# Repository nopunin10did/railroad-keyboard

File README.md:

# The Railroad Keyboard
PCB and Plate Repository

A long keyboard with ortholinear alphas and semi-standard modifier keys. For more information, join the [NoPunIn10Key Discord](https://discord.gg/7AcdaNw5Fn).

* Keyboard Maintainer: [NoPunIn10Did](https://nopunin10did.com)
* Hardware Supported: The Railroad: 2020-07 Prototype

This repository contains the KiCad files for the PCB, switch plate, and bottom plate. It also contains the BOM files that I used when ordering it from JLCPCB.

This work (Railroad Keyboard) is licensed under a [Creative Commons Attribution-ShareAlike 4.0 International License](https://creativecommons.org/licenses/by-sa/4.0/).

All other rights are reserved by NoPunIn10Did LLC.

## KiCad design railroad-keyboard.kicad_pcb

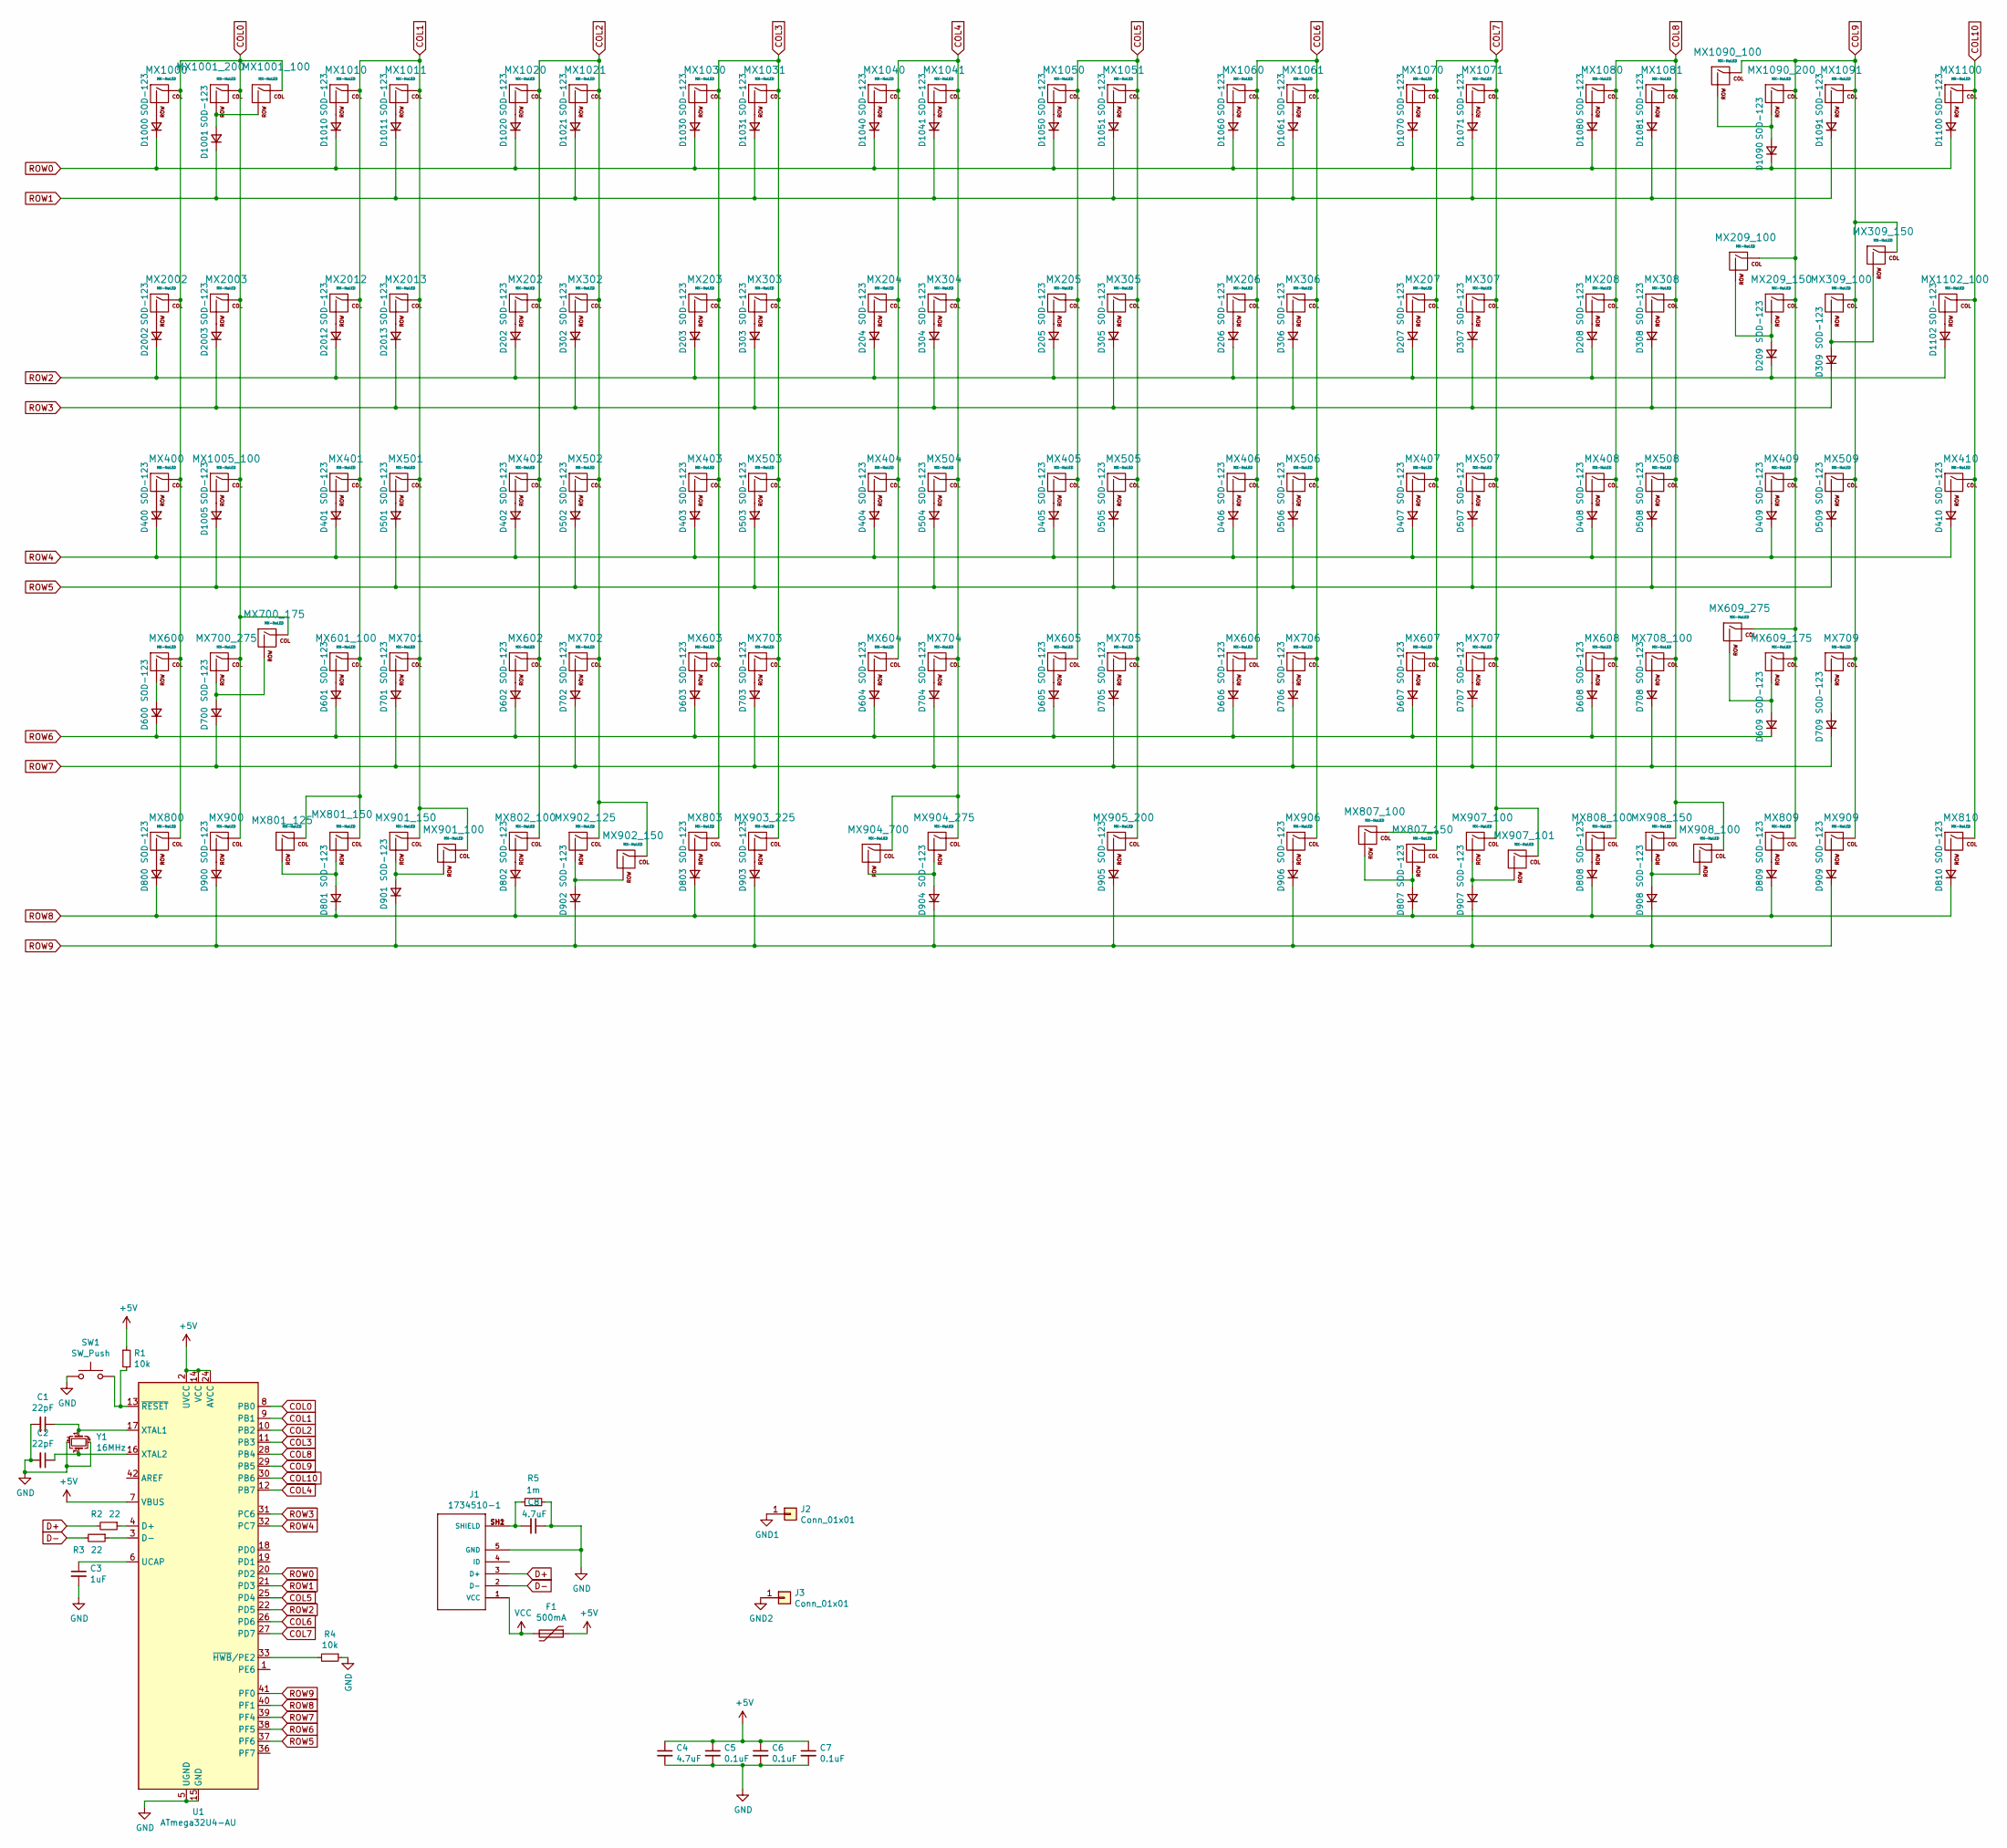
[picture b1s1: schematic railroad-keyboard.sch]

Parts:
C1, C2: 22pF; C_0805_2012Metric
C3: 1uF; C_0805_2012Metric
C4, C8: 4.7uF; C_0805_2012Metric
C5, C6, C7: 0.1uF; C_0805_2012Metric
D202, D203, D204, D205, D206, D207, D208, D209, D302, D303, D304, D305, D306, D307, D308, D309, D400, D401, D402, D403, D404, D405, D406, D407, D408, D409, D410, D501, D502, D503, D504, D505, D506, D507, D508, D509, D600, D601, D602, D603, D604, D605, D606, D607, D608, D609, D700, D701, D702, D703, D704, D705, D706, D707, D708, D709, D800, D801, D802, D803, D807, D808, D809, D810, D900, D901, D902, D903, D904, D905, D906, D907, D908, D909, D1000, D1001, D1005, D1010, D1011, D1020, D1021, D1030, D1031, D1040, D1041, D1050, D1051, D1060, D1061, D1070, D1071, D1080, D1081, D1090, D1091, D1100, D1102, D2002, D2003, D2012, D2013: SOD-123; D_SOD-123
F1: 500mA; Fuse_1206_3216Metric
J1: 1734510-1; TE_1734510-1
J2, J3: Conn_01x01; PinHeader_1x01_P1.00mm_Horizontal
MX202, MX203, MX204, MX205, MX206, MX207, MX208, MX209_100, MX302, MX303, MX304, MX305, MX306, MX307, MX308, MX309_100, MX402, MX403, MX404, MX405, MX406, MX407, MX408, MX409, MX501, MX502, MX503, MX504, MX505, MX506, MX507, MX508, MX600, MX601_100, MX602, MX603, MX604, MX605, MX606, MX607, MX608, MX701, MX702, MX703, MX704, MX705, MX706, MX707, MX708_100, MX709, MX800, MX802_100, MX803, MX807_100, MX808_100, MX809, MX810, MX900, MX901_100, MX906, MX907_100, MX907_101, MX908_100, MX909, MX1000, MX1001_100, MX1005_100, MX1010, MX1011, MX1020, MX1021, MX1030, MX1031, MX1040, MX1041, MX1050, MX1051, MX1060, MX1061, MX1070, MX1071, MX1080, MX1081, MX1090_100, MX1091, MX1100, MX1102_100, MX2002, MX2013: MX-NoLED; MXOnly-1U-NoLED
MX209_150, MX309_150, MX801_150, MX807_150, MX901_150, MX902_150, MX908_150, MX2003, MX2012: MX-NoLED; MXOnly-1.5U-NoLED
MX400, MX801_125, MX902_125: MX-NoLED; MXOnly-1.25U-NoLED
MX401, MX903_225: MX-NoLED; MXOnly-2.25U-NoLED
MX410: MX-NoLED; MXOnly-ISO-ROTATED-ReversedStabilizers-NoLED
MX509, MX609_175, MX700_175: MX-NoLED; MXOnly-1.75U-NoLED
MX609_275, MX700_275: MX-NoLED; MXOnly-2.75U-NoLED
MX904_275: MX-NoLED; MXOnly-2.75U-ReversedStabilizers-NoLED
MX904_700: MX-NoLED; MXOnly-7U-NoLED
MX905_200, MX1001_200, MX1090_200: MX-NoLED; MXOnly-2U-NoLED
R1, R4: 10k; R_0805_2012Metric
R2, R3: 22; R_0805_2012Metric
R5: 1m; R_0805_2012Metric
SW1: SW_Push; SW_Tactile_SPST_Angled_MJTP1117
U1: ATmega32U4-AU; TQFP-44_10x10mm_P0.8mm
Y1: 16MHz; Crystal_SMD_3225-4Pin_3.2x2.5mm

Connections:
+5V: C4.1, C5.1, C6.1, C7.1, F1.1, R1.1, U1.2 (UVCC), U1.7 (VBUS), U1.14 (VCC), U1.24 (AVCC), U1.34 (VCC), U1.44 (AVCC)
COL0: MX400.1 (COL), MX600.1 (COL), MX700_175.1 (COL), MX700_275.1 (COL), MX800.1 (COL), MX900.1 (COL), MX1000.1 (COL), MX1001_100.1 (COL), MX1001_200.1 (COL), MX1005_100.1 (COL), MX2002.1 (COL), MX2003.1 (COL), U1.8 (PB0); also elsewhere on the board
COL1: MX401.1 (COL), MX501.1 (COL), MX601_100.1 (COL), MX701.1 (COL), MX801_125.1 (COL), MX801_150.1 (COL), MX901_100.1 (COL), MX901_150.1 (COL), MX1010.1 (COL), MX1011.1 (COL), MX2012.1 (COL), MX2013.1 (COL), U1.9 (PB1); also elsewhere on the board
COL2: MX202.1 (COL), MX302.1 (COL), MX402.1 (COL), MX502.1 (COL), MX602.1 (COL), MX702.1 (COL), MX802_100.1 (COL), MX902_125.1 (COL), MX902_150.1 (COL), MX1020.1 (COL), MX1021.1 (COL), U1.10 (PB2)
COL3: MX203.1 (COL), MX303.1 (COL), MX403.1 (COL), MX503.1 (COL), MX603.1 (COL), MX703.1 (COL), MX803.1 (COL), MX903_225.1 (COL), MX1030.1 (COL), MX1031.1 (COL), U1.11 (PB3)
COL4: MX204.1 (COL), MX304.1 (COL), MX404.1 (COL), MX504.1 (COL), MX604.1 (COL), MX704.1 (COL), MX904_275.1 (COL), MX904_700.1 (COL), MX1040.1 (COL), MX1041.1 (COL), U1.12 (PB7)
COL5: MX205.1 (COL), MX305.1 (COL), MX405.1 (COL), MX505.1 (COL), MX605.1 (COL), MX705.1 (COL), MX905_200.1 (COL), MX1050.1 (COL), MX1051.1 (COL), U1.25 (PD4)
COL6: MX206.1 (COL), MX306.1 (COL), MX406.1 (COL), MX506.1 (COL), MX606.1 (COL), MX706.1 (COL), MX906.1 (COL), MX1060.1 (COL), MX1061.1 (COL), U1.26 (PD6)
COL7: MX207.1 (COL), MX307.1 (COL), MX407.1 (COL), MX507.1 (COL), MX607.1 (COL), MX707.1 (COL), MX807_100.1 (COL), MX807_150.1 (COL), MX907_100.1 (COL), MX907_101.1 (COL), MX1070.1 (COL), MX1071.1 (COL), U1.27 (PD7)
COL8: MX208.1 (COL), MX308.1 (COL), MX408.1 (COL), MX508.1 (COL), MX608.1 (COL), MX708_100.1 (COL), MX808_100.1 (COL), MX908_100.1 (COL), MX908_150.1 (COL), MX1080.1 (COL), MX1081.1 (COL), U1.28 (PB4)
COL9: MX209_100.1 (COL), MX209_150.1 (COL), MX309_100.1 (COL), MX309_150.1 (COL), MX409.1 (COL), MX509.1 (COL), MX609_175.1 (COL), MX609_275.1 (COL), MX709.1 (COL), MX809.1 (COL), MX909.1 (COL), MX1090_100.1 (COL), MX1090_200.1 (COL), MX1091.1 (COL), U1.29 (PB5)
COL10: MX410.1 (COL), MX810.1 (COL), MX1100.1 (COL), MX1102_100.1 (COL), U1.30 (PB6)
D+: J1.3 (D+), R2.2
D-: J1.2 (D-), R3.2
GND: C1.2, C2.2, C3.2, C4.2, C5.2, C6.2, C7.2, C8.1, J1.5 (GND), R4.1, R5.2, SW1.1, U1.5 (UGND), U1.15 (GND), U1.23 (GND), U1.35 (GND), U1.43 (GND), Y1.2, Y1.4
GND1: J2.1
GND2: J3.1
unnamed: C1.1, U1.17 (XTAL1), Y1.1
unnamed: C2.1, U1.16 (XTAL2), Y1.3
unnamed: C3.1, U1.6 (UCAP)
unnamed: C8.2, J1.SH1 (SHIELD), J1.SH2 (SHIELD), R5.1
unnamed: D202.2 (A), MX202.2 (ROW)
unnamed: D203.2 (A), MX203.2 (ROW)
unnamed: D204.2 (A), MX204.2 (ROW)
unnamed: D205.2 (A), MX205.2 (ROW)
unnamed: D206.2 (A), MX206.2 (ROW)
unnamed: D207.2 (A), MX207.2 (ROW)
unnamed: D208.2 (A), MX208.2 (ROW)
unnamed: D209.2 (A), MX209_100.2 (ROW), MX209_150.2 (ROW)
unnamed: D302.2 (A), MX302.2 (ROW)
unnamed: D303.2 (A), MX303.2 (ROW)
unnamed: D304.2 (A), MX304.2 (ROW)
unnamed: D305.2 (A), MX305.2 (ROW)
unnamed: D306.2 (A), MX306.2 (ROW)
unnamed: D307.2 (A), MX307.2 (ROW)
unnamed: D308.2 (A), MX308.2 (ROW)
unnamed: D309.2 (A), MX309_100.2 (ROW), MX309_150.2 (ROW)
unnamed: D400.2 (A), MX400.2 (ROW)
unnamed: D401.2 (A), MX401.2 (ROW)
unnamed: D402.2 (A), MX402.2 (ROW)
unnamed: D403.2 (A), MX403.2 (ROW)
unnamed: D404.2 (A), MX404.2 (ROW)
unnamed: D405.2 (A), MX405.2 (ROW)
unnamed: D406.2 (A), MX406.2 (ROW)
unnamed: D407.2 (A), MX407.2 (ROW)
unnamed: D408.2 (A), MX408.2 (ROW)
unnamed: D409.2 (A), MX409.2 (ROW)
unnamed: D410.2 (A), MX410.2 (ROW)
unnamed: D501.2 (A), MX501.2 (ROW)
unnamed: D502.2 (A), MX502.2 (ROW)
unnamed: D503.2 (A), MX503.2 (ROW)
unnamed: D504.2 (A), MX504.2 (ROW)
unnamed: D505.2 (A), MX505.2 (ROW)
unnamed: D506.2 (A), MX506.2 (ROW)
unnamed: D507.2 (A), MX507.2 (ROW)
unnamed: D508.2 (A), MX508.2 (ROW)
unnamed: D509.2 (A), MX509.2 (ROW)
unnamed: D600.2 (A), MX600.2 (ROW)
unnamed: D601.2 (A), MX601_100.2 (ROW)
unnamed: D602.2 (A), MX602.2 (ROW)
unnamed: D603.2 (A), MX603.2 (ROW)
unnamed: D604.2 (A), MX604.2 (ROW)
unnamed: D605.2 (A), MX605.2 (ROW)
unnamed: D606.2 (A), MX606.2 (ROW)
unnamed: D607.2 (A), MX607.2 (ROW)
unnamed: D608.2 (A), MX608.2 (ROW)
unnamed: D609.2 (A), MX609_175.2 (ROW), MX609_275.2 (ROW)
unnamed: D700.2 (A), MX700_175.2 (ROW), MX700_275.2 (ROW)
unnamed: D701.2 (A), MX701.2 (ROW)
unnamed: D702.2 (A), MX702.2 (ROW)
unnamed: D703.2 (A), MX703.2 (ROW)
unnamed: D704.2 (A), MX704.2 (ROW)
unnamed: D705.2 (A), MX705.2 (ROW)
unnamed: D706.2 (A), MX706.2 (ROW)
unnamed: D707.2 (A), MX707.2 (ROW)
unnamed: D708.2 (A), MX708_100.2 (ROW)
unnamed: D709.2 (A), MX709.2 (ROW)
unnamed: D800.2 (A), MX800.2 (ROW)
unnamed: D801.2 (A), MX801_125.2 (ROW), MX801_150.2 (ROW)
unnamed: D802.2 (A), MX802_100.2 (ROW)
unnamed: D803.2 (A), MX803.2 (ROW)
unnamed: D807.2 (A), MX807_100.2 (ROW), MX807_150.2 (ROW)
unnamed: D808.2 (A), MX808_100.2 (ROW)
unnamed: D809.2 (A), MX809.2 (ROW)
unnamed: D810.2 (A), MX810.2 (ROW)
unnamed: D900.2 (A), MX900.2 (ROW)
unnamed: D901.2 (A), MX901_100.2 (ROW), MX901_150.2 (ROW)
unnamed: D902.2 (A), MX902_125.2 (ROW), MX902_150.2 (ROW)
unnamed: D903.2 (A), MX903_225.2 (ROW)
unnamed: D904.2 (A), MX904_275.2 (ROW), MX904_700.2 (ROW)
unnamed: D905.2 (A), MX905_200.2 (ROW)
unnamed: D906.2 (A), MX906.2 (ROW)
unnamed: D907.2 (A), MX907_100.2 (ROW), MX907_101.2 (ROW)
unnamed: D908.2 (A), MX908_100.2 (ROW), MX908_150.2 (ROW)
unnamed: D909.2 (A), MX909.2 (ROW)
unnamed: D1000.2 (A), MX1000.2 (ROW)
unnamed: D1001.2 (A), MX1001_100.2 (ROW), MX1001_200.2 (ROW)
unnamed: D1005.2 (A), MX1005_100.2 (ROW)
unnamed: D1010.2 (A), MX1010.2 (ROW)
unnamed: D1011.2 (A), MX1011.2 (ROW)
unnamed: D1020.2 (A), MX1020.2 (ROW)
unnamed: D1021.2 (A), MX1021.2 (ROW)
unnamed: D1030.2 (A), MX1030.2 (ROW)
unnamed: D1031.2 (A), MX1031.2 (ROW)
unnamed: D1040.2 (A), MX1040.2 (ROW)
unnamed: D1041.2 (A), MX1041.2 (ROW)
unnamed: D1050.2 (A), MX1050.2 (ROW)
unnamed: D1051.2 (A), MX1051.2 (ROW)
unnamed: D1060.2 (A), MX1060.2 (ROW)
unnamed: D1061.2 (A), MX1061.2 (ROW)
unnamed: D1070.2 (A), MX1070.2 (ROW)
unnamed: D1071.2 (A), MX1071.2 (ROW)
unnamed: D1080.2 (A), MX1080.2 (ROW)
unnamed: D1081.2 (A), MX1081.2 (ROW)
unnamed: D1090.2 (A), MX1090_100.2 (ROW), MX1090_200.2 (ROW)
unnamed: D1091.2 (A), MX1091.2 (ROW)
unnamed: D1100.2 (A), MX1100.2 (ROW)
unnamed: D1102.2 (A), MX1102_100.2 (ROW)
unnamed: D2002.2 (A), MX2002.2 (ROW)
unnamed: D2003.2 (A), MX2003.2 (ROW)
unnamed: D2012.2 (A), MX2012.2 (ROW)
unnamed: D2013.2 (A), MX2013.2 (ROW)
unnamed: R1.2, SW1.2, U1.13 (~RESET)
unnamed: R2.1, U1.4 (D+)
unnamed: R3.1, U1.3 (D-)
unnamed: R4.2, U1.33 (~HWB~/PE2)
ROW0: D1000.1 (K), D1010.1 (K), D1020.1 (K), D1030.1 (K), D1040.1 (K), D1050.1 (K), D1060.1 (K), D1070.1 (K), D1080.1 (K), D1090.1 (K), D1100.1 (K), U1.20 (PD2)
ROW1: D1001.1 (K), D1011.1 (K), D1021.1 (K), D1031.1 (K), D1041.1 (K), D1051.1 (K), D1061.1 (K), D1071.1 (K), D1081.1 (K), D1091.1 (K), U1.21 (PD3)
ROW2: D202.1 (K), D203.1 (K), D204.1 (K), D205.1 (K), D206.1 (K), D207.1 (K), D208.1 (K), D209.1 (K), D1102.1 (K), D2002.1 (K), D2012.1 (K), U1.22 (PD5); also elsewhere on the board
ROW3: D302.1 (K), D303.1 (K), D304.1 (K), D305.1 (K), D306.1 (K), D307.1 (K), D308.1 (K), D309.1 (K), D2003.1 (K), D2013.1 (K), U1.31 (PC6); also elsewhere on the board
ROW4: D400.1 (K), D401.1 (K), D402.1 (K), D403.1 (K), D404.1 (K), D405.1 (K), D406.1 (K), D407.1 (K), D408.1 (K), D409.1 (K), D410.1 (K), U1.32 (PC7)
ROW5: D501.1 (K), D502.1 (K), D503.1 (K), D504.1 (K), D505.1 (K), D506.1 (K), D507.1 (K), D508.1 (K), D509.1 (K), D1005.1 (K), U1.37 (PF6); also elsewhere on the board
ROW6: D600.1 (K), D601.1 (K), D602.1 (K), D603.1 (K), D604.1 (K), D605.1 (K), D606.1 (K), D607.1 (K), D608.1 (K), D609.1 (K), U1.38 (PF5)
ROW7: D700.1 (K), D701.1 (K), D702.1 (K), D703.1 (K), D704.1 (K), D705.1 (K), D706.1 (K), D707.1 (K), D708.1 (K), D709.1 (K), U1.39 (PF4)
ROW8: D800.1 (K), D801.1 (K), D802.1 (K), D803.1 (K), D807.1 (K), D808.1 (K), D809.1 (K), D810.1 (K), U1.40 (PF1)
ROW9: D900.1 (K), D901.1 (K), D902.1 (K), D903.1 (K), D904.1 (K), D905.1 (K), D906.1 (K), D907.1 (K), D908.1 (K), D909.1 (K), U1.41 (PF0)
VCC: F1.2, J1.1 (VCC)

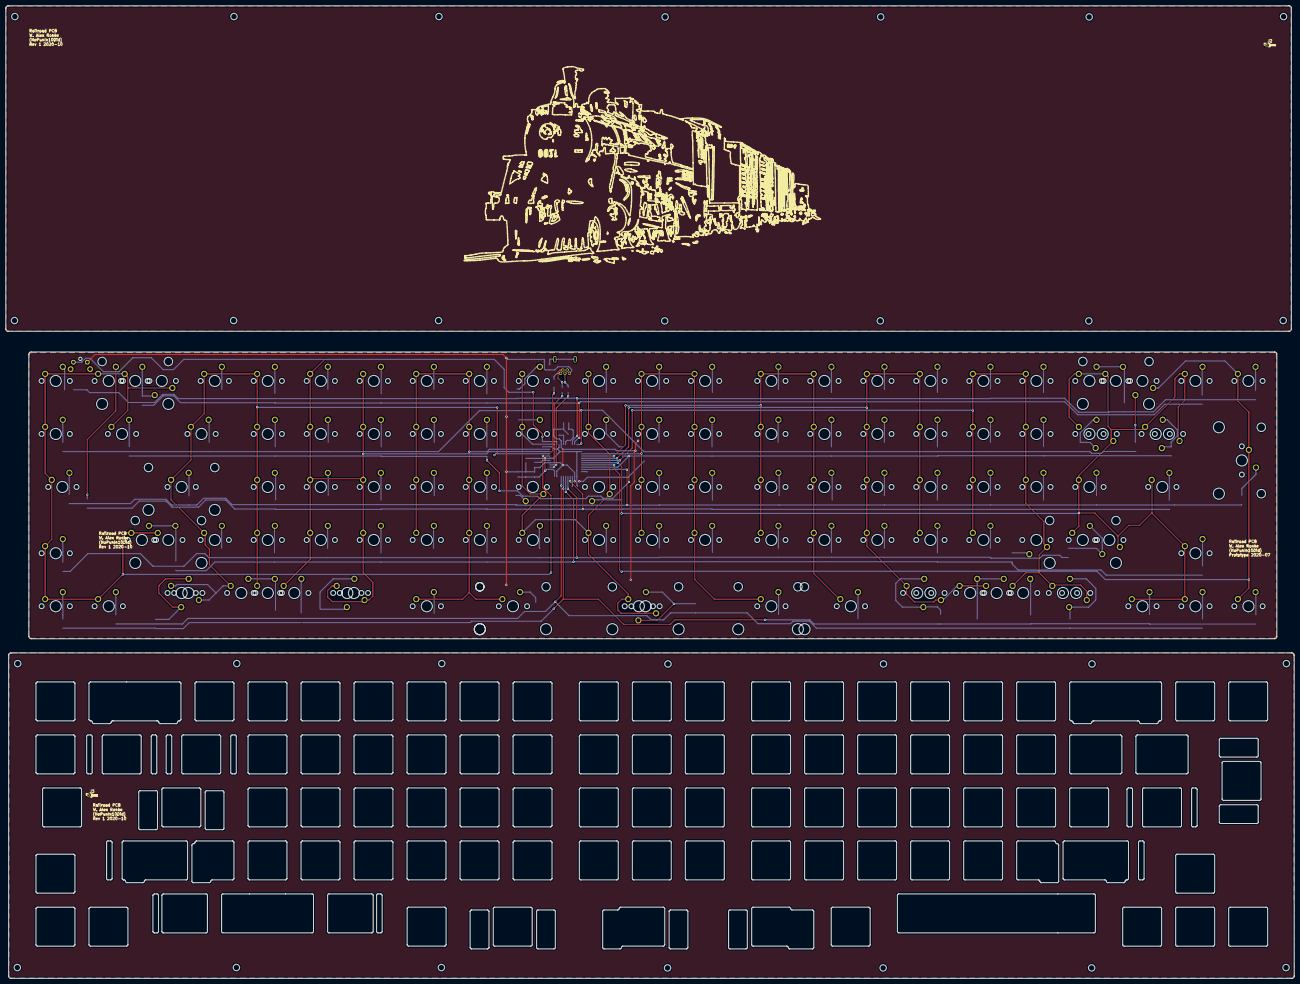
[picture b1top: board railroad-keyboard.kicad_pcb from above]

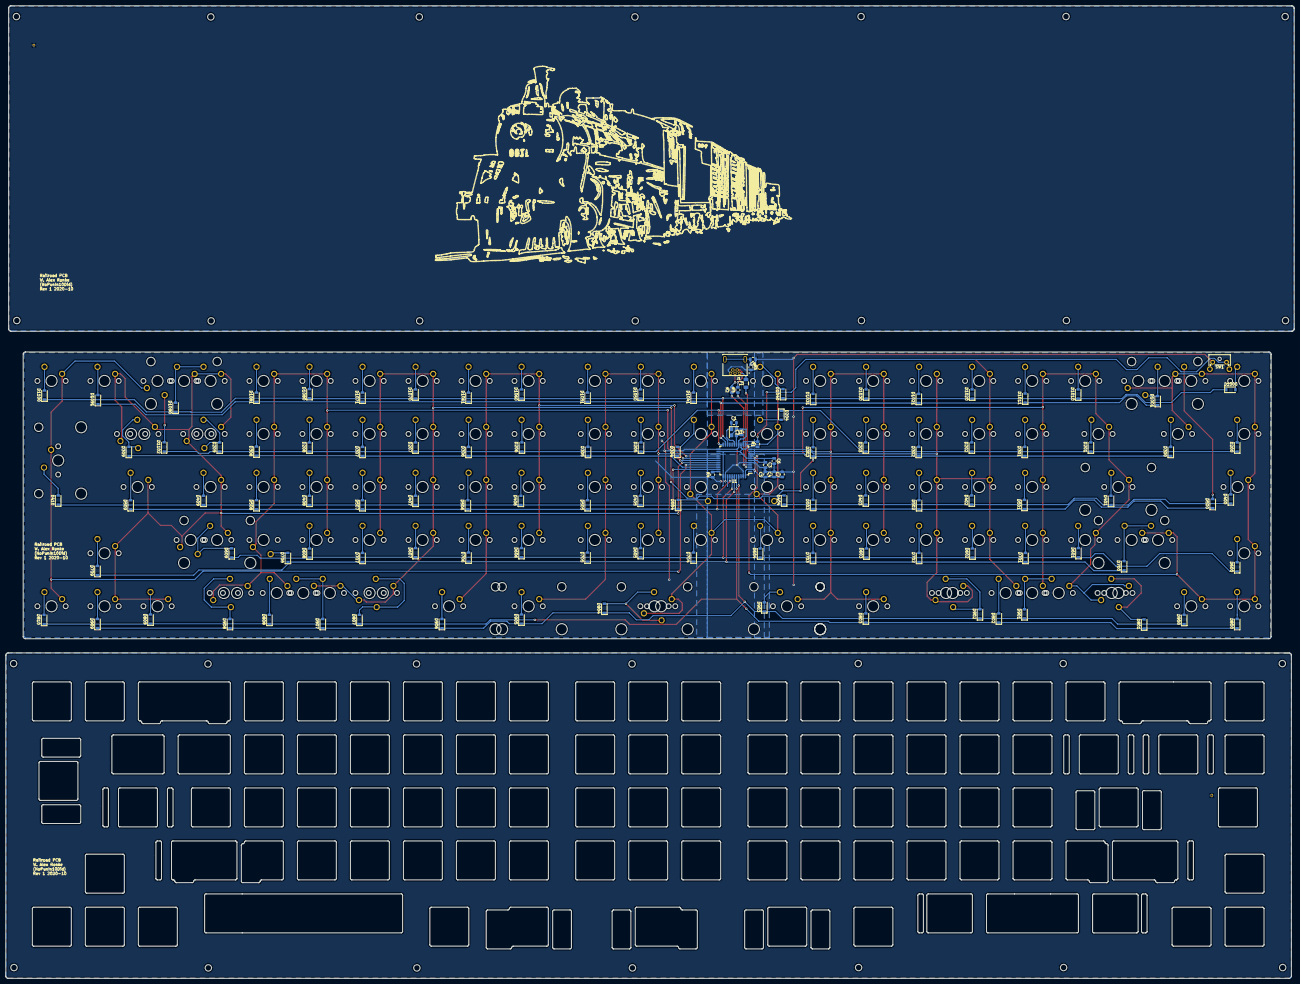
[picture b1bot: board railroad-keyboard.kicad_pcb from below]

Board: 2 copper layers, 448.5 x 103.0 mm, 235 parts (119 on the bottom side), 135 nets.

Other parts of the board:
D200, D201, D300, D301, D500: SOD-123; D_SOD-123
MX200, MX301, MX500_100: MX-NoLED; MXOnly-1U-NoLED
MX201, MX300: MX-NoLED; MXOnly-1.5U-NoLED

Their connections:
COL0: MX200.1, MX300.1, MX500_100.1; also elsewhere on the board
COL1: MX201.1, MX301.1; also elsewhere on the board
unnamed: D200.2, MX200.2
unnamed: D201.2, MX201.2
unnamed: D300.2, MX300.2
unnamed: D301.2, MX301.2
unnamed: D500.2, MX500_100.2
ROW2: D200.1, D201.1; also elsewhere on the board
ROW3: D300.1, D301.1; also elsewhere on the board
ROW5: D500.1; also elsewhere on the board

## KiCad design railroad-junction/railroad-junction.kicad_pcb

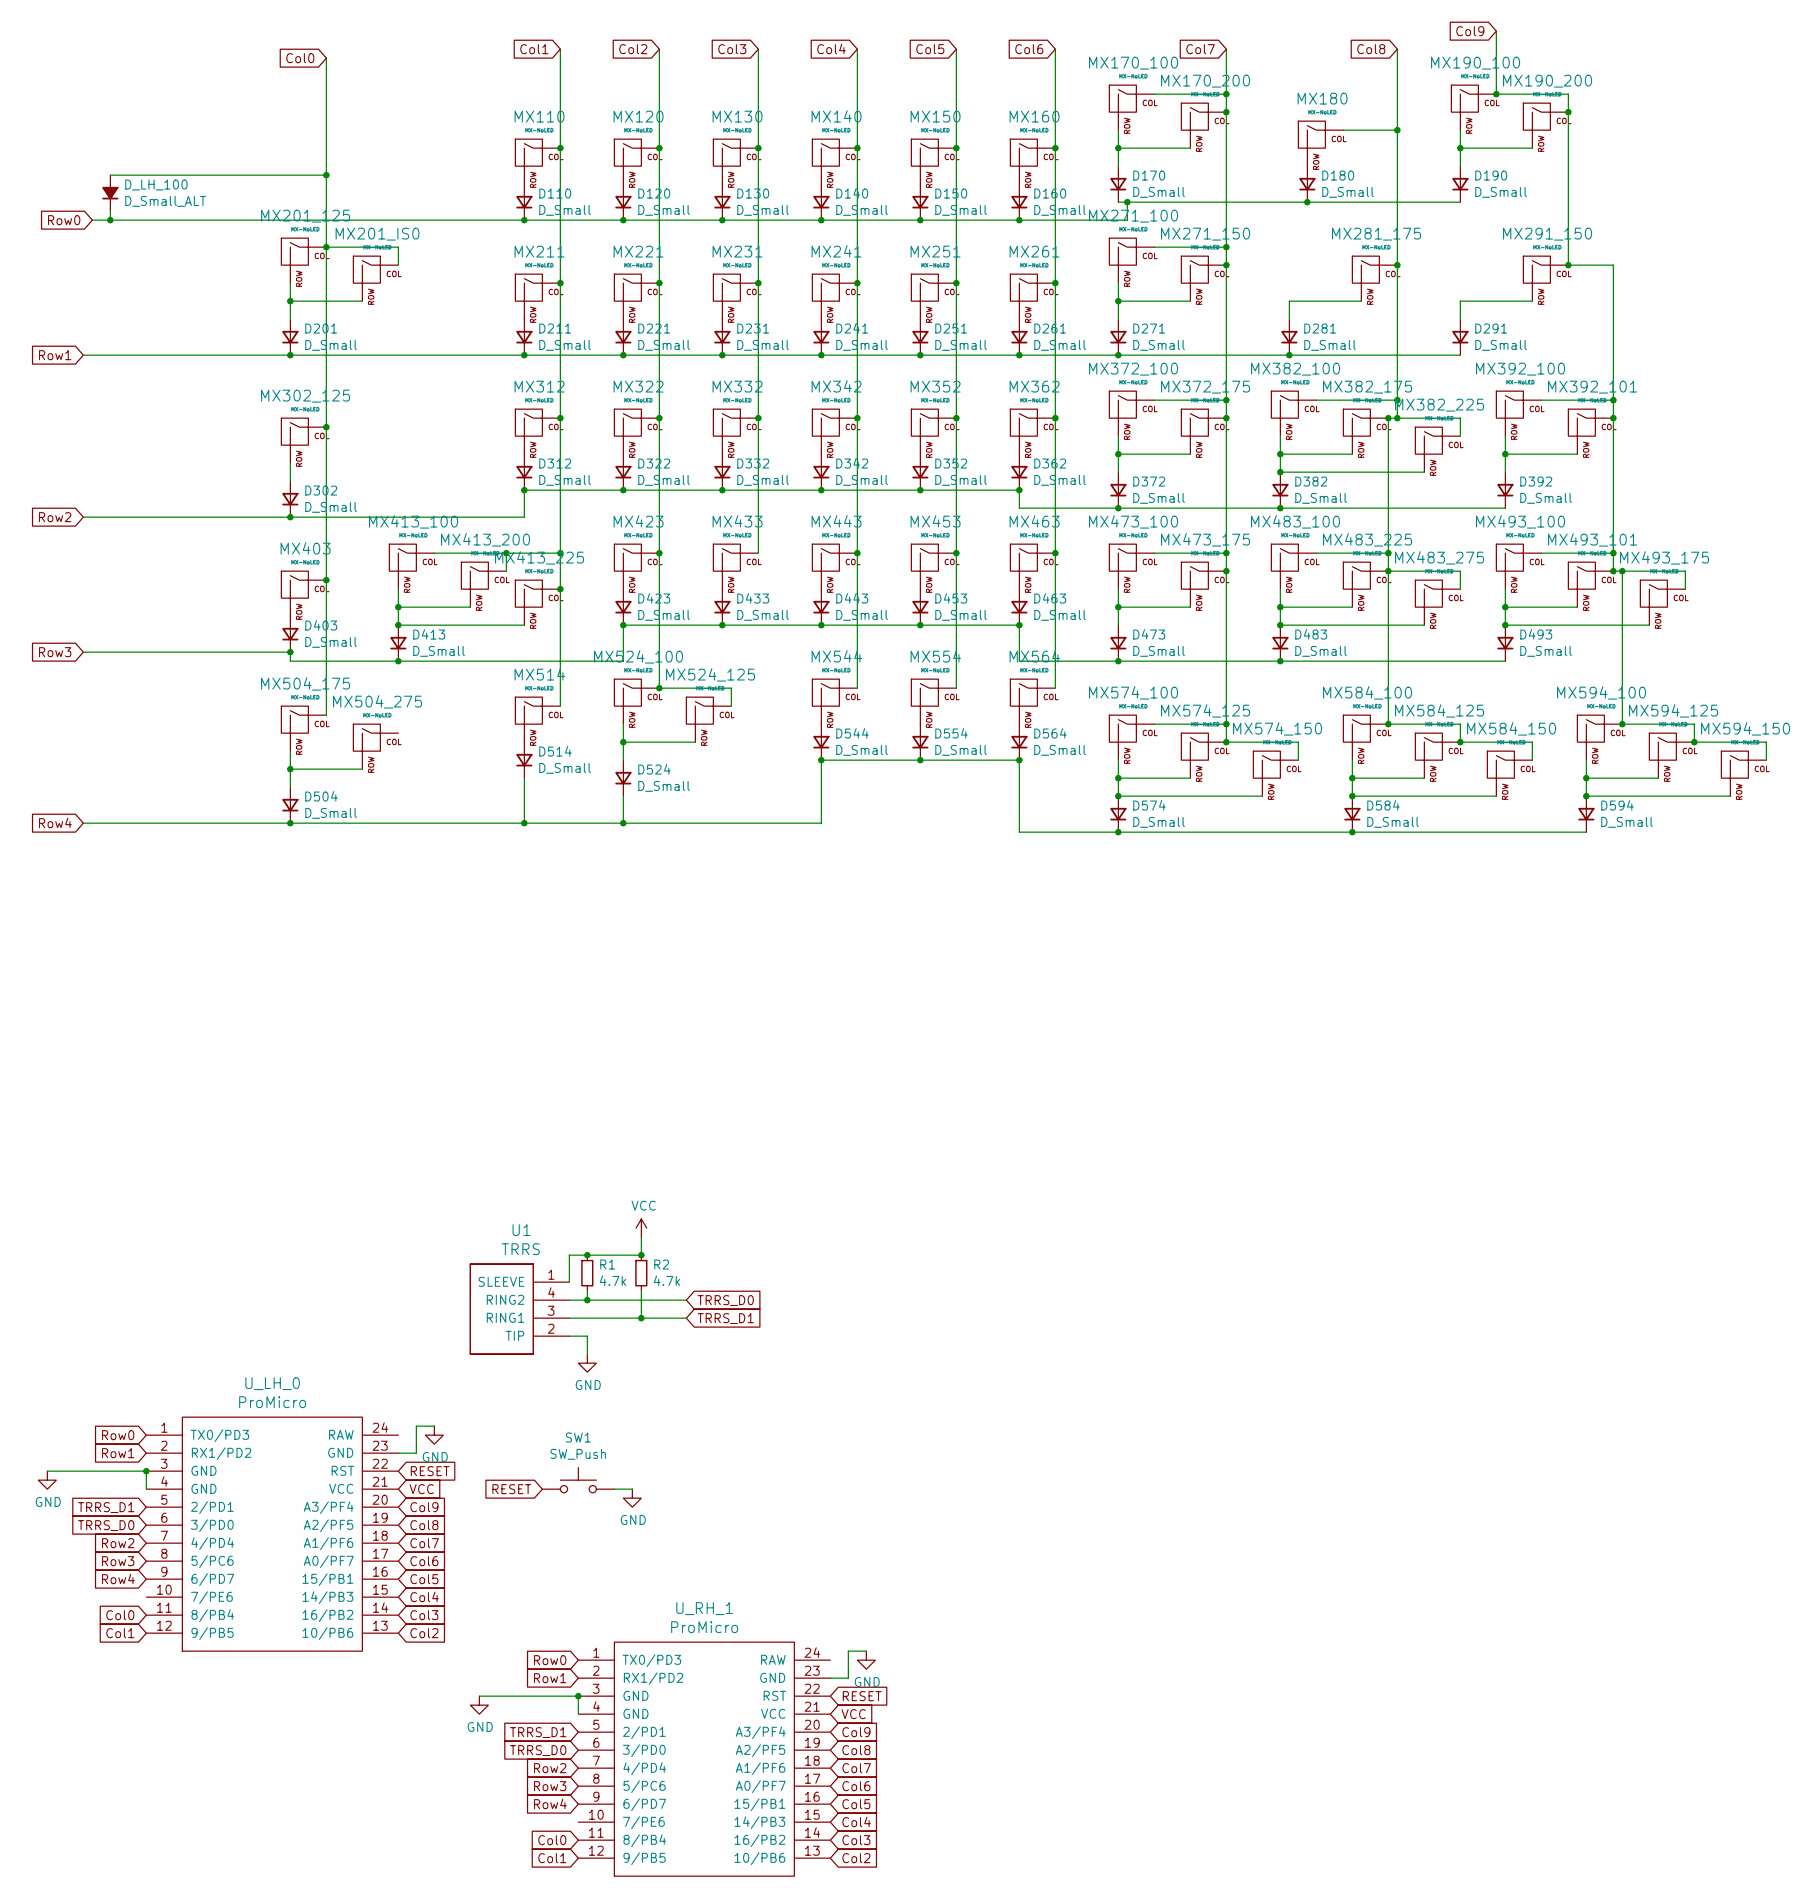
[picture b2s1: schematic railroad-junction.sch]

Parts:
D110, D120, D130, D140, D150, D160, D170, D180, D190, D201, D211, D221, D231, D241, D251, D261, D271, D281, D291, D302, D312, D322, D332, D342, D352, D362, D372, D382, D392, D403, D413, D423, D433, D443, D453, D463, D473, D483, D493, D504, D514, D524, D544, D554, D564, D574, D584, D594: D_Small; Diode
D_LH_100: D_Small_ALT; Diode
MX110, MX120, MX130, MX140, MX150, MX160, MX170_100, MX180, MX190_100, MX211, MX221, MX231, MX241, MX251, MX261, MX271_100, MX312, MX322, MX332, MX342, MX352, MX362, MX372_100, MX382_100, MX392_100, MX392_101, MX403, MX413_100, MX423, MX433, MX443, MX453, MX463, MX473_100, MX483_100, MX493_100, MX493_101, MX514, MX524_100, MX544, MX554, MX564, MX574_100, MX584_100, MX594_100: MX-NoLED; MXOnly-1U-Symmetric
MX170_200, MX190_200, MX413_200: MX-NoLED; MXOnly-2U-Symmetric
MX201_125, MX302_125, MX524_125, MX574_125, MX584_125, MX594_125: MX-NoLED; MXOnly-1.25U-Symmetric
MX201_IS0: MX-NoLED; MXOnly-ISO-ROTATED-ReversedStabilizers-Symmetric
MX271_150, MX291_150, MX574_150, MX584_150, MX594_150: MX-NoLED; MXOnly-1.5U-Symmetric
MX281_175, MX372_175, MX382_175, MX473_175, MX493_175, MX504_175: MX-NoLED; MXOnly-1.75U-Symmetric
MX382_225, MX413_225, MX483_225: MX-NoLED; MXOnly-2.25U-Symmetric
MX483_275, MX504_275: MX-NoLED; MXOnly-2.75U-Symmetric
R1, R2: 4.7k; Resistor
SW1: SW_Push; SW_Tactile_SPST_Angled_MJTP1117
U1: TRRS; TRRS-PJ-320A-dual
U_LH_0: ProMicro; ArduinoProMicro
U_RH_1: ProMicro; ArduinoProMicro

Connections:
Col0: D_LH_100.2 (A), MX201_125.1 (COL), MX201_IS0.1 (COL), MX302_125.1 (COL), MX403.1 (COL), MX504_175.1 (COL), U_LH_0.11 (8/PB4), U_RH_1.11 (8/PB4)
Col1: MX110.1 (COL), MX211.1 (COL), MX312.1 (COL), MX413_100.1 (COL), MX413_200.1 (COL), MX413_225.1 (COL), MX514.1 (COL), U_LH_0.12 (9/PB5), U_RH_1.12 (9/PB5)
Col2: MX120.1 (COL), MX221.1 (COL), MX322.1 (COL), MX423.1 (COL), MX524_100.1 (COL), MX524_125.1 (COL), U_LH_0.13 (10/PB6), U_RH_1.13 (10/PB6)
Col3: MX130.1 (COL), MX231.1 (COL), MX332.1 (COL), MX433.1 (COL), U_LH_0.14 (16/PB2), U_RH_1.14 (16/PB2)
Col4: MX140.1 (COL), MX241.1 (COL), MX342.1 (COL), MX443.1 (COL), MX544.1 (COL), U_LH_0.15 (14/PB3), U_RH_1.15 (14/PB3)
Col5: MX150.1 (COL), MX251.1 (COL), MX352.1 (COL), MX453.1 (COL), MX554.1 (COL), U_LH_0.16 (15/PB1), U_RH_1.16 (15/PB1)
Col6: MX160.1 (COL), MX261.1 (COL), MX362.1 (COL), MX463.1 (COL), MX564.1 (COL), U_LH_0.17 (A0/PF7), U_RH_1.17 (A0/PF7)
Col7: MX170_100.1 (COL), MX170_200.1 (COL), MX271_100.1 (COL), MX271_150.1 (COL), MX372_100.1 (COL), MX372_175.1 (COL), MX473_100.1 (COL), MX473_175.1 (COL), MX574_100.1 (COL), MX574_125.1 (COL), MX574_150.1 (COL), U_LH_0.18 (A1/PF6), U_RH_1.18 (A1/PF6)
Col8: MX180.1 (COL), MX281_175.1 (COL), MX382_100.1 (COL), MX382_175.1 (COL), MX382_225.1 (COL), MX483_100.1 (COL), MX483_225.1 (COL), MX483_275.1 (COL), MX584_100.1 (COL), MX584_125.1 (COL), MX584_150.1 (COL), U_LH_0.19 (A2/PF5), U_RH_1.19 (A2/PF5)
Col9: MX190_100.1 (COL), MX190_200.1 (COL), MX291_150.1 (COL), MX392_100.1 (COL), MX392_101.1 (COL), MX493_100.1 (COL), MX493_101.1 (COL), MX493_175.1 (COL), MX594_100.1 (COL), MX594_125.1 (COL), MX594_150.1 (COL), U_LH_0.20 (A3/PF4), U_RH_1.20 (A3/PF4)
GND: SW1.2, U1.2 (TIP), U_LH_0.3 (GND), U_LH_0.4 (GND), U_LH_0.23 (GND), U_RH_1.3 (GND), U_RH_1.4 (GND), U_RH_1.23 (GND)
unnamed: D110.2 (A), MX110.2 (ROW)
unnamed: D120.2 (A), MX120.2 (ROW)
unnamed: D130.2 (A), MX130.2 (ROW)
unnamed: D140.2 (A), MX140.2 (ROW)
unnamed: D150.2 (A), MX150.2 (ROW)
unnamed: D160.2 (A), MX160.2 (ROW)
unnamed: D170.2 (A), MX170_100.2 (ROW), MX170_200.2 (ROW)
unnamed: D180.2 (A), MX180.2 (ROW)
unnamed: D190.2 (A), MX190_100.2 (ROW), MX190_200.2 (ROW)
unnamed: D201.2 (A), MX201_125.2 (ROW), MX201_IS0.2 (ROW)
unnamed: D211.2 (A), MX211.2 (ROW)
unnamed: D221.2 (A), MX221.2 (ROW)
unnamed: D231.2 (A), MX231.2 (ROW)
unnamed: D241.2 (A), MX241.2 (ROW)
unnamed: D251.2 (A), MX251.2 (ROW)
unnamed: D261.2 (A), MX261.2 (ROW)
unnamed: D271.2 (A), MX271_100.2 (ROW), MX271_150.2 (ROW)
unnamed: D281.2 (A), MX281_175.2 (ROW)
unnamed: D291.2 (A), MX291_150.2 (ROW)
unnamed: D302.2 (A), MX302_125.2 (ROW)
unnamed: D312.2 (A), MX312.2 (ROW)
unnamed: D322.2 (A), MX322.2 (ROW)
unnamed: D332.2 (A), MX332.2 (ROW)
unnamed: D342.2 (A), MX342.2 (ROW)
unnamed: D352.2 (A), MX352.2 (ROW)
unnamed: D362.2 (A), MX362.2 (ROW)
unnamed: D372.2 (A), MX372_100.2 (ROW), MX372_175.2 (ROW)
unnamed: D382.2 (A), MX382_100.2 (ROW), MX382_175.2 (ROW), MX382_225.2 (ROW)
unnamed: D392.2 (A), MX392_100.2 (ROW), MX392_101.2 (ROW)
unnamed: D403.2 (A), MX403.2 (ROW)
unnamed: D413.2 (A), MX413_100.2 (ROW), MX413_200.2 (ROW), MX413_225.2 (ROW)
unnamed: D423.2 (A), MX423.2 (ROW)
unnamed: D433.2 (A), MX433.2 (ROW)
unnamed: D443.2 (A), MX443.2 (ROW)
unnamed: D453.2 (A), MX453.2 (ROW)
unnamed: D463.2 (A), MX463.2 (ROW)
unnamed: D473.2 (A), MX473_100.2 (ROW), MX473_175.2 (ROW)
unnamed: D483.2 (A), MX483_100.2 (ROW), MX483_225.2 (ROW), MX483_275.2 (ROW)
unnamed: D493.2 (A), MX493_100.2 (ROW), MX493_101.2 (ROW), MX493_175.2 (ROW)
unnamed: D504.2 (A), MX504_175.2 (ROW), MX504_275.2 (ROW)
unnamed: D514.2 (A), MX514.2 (ROW)
unnamed: D524.2 (A), MX524_100.2 (ROW), MX524_125.2 (ROW)
unnamed: D544.2 (A), MX544.2 (ROW)
unnamed: D554.2 (A), MX554.2 (ROW)
unnamed: D564.2 (A), MX564.2 (ROW)
unnamed: D574.2 (A), MX574_100.2 (ROW), MX574_125.2 (ROW), MX574_150.2 (ROW)
unnamed: D584.2 (A), MX584_100.2 (ROW), MX584_125.2 (ROW), MX584_150.2 (ROW)
unnamed: D594.2 (A), MX594_100.2 (ROW), MX594_125.2 (ROW), MX594_150.2 (ROW)
RESET: SW1.1, U_LH_0.22 (RST), U_RH_1.22 (RST)
Row0: D110.1 (K), D120.1 (K), D130.1 (K), D140.1 (K), D150.1 (K), D160.1 (K), D170.1 (K), D180.1 (K), D190.1 (K), D_LH_100.1 (K), U_LH_0.1 (TX0/PD3), U_RH_1.1 (TX0/PD3)
Row1: D201.1 (K), D211.1 (K), D221.1 (K), D231.1 (K), D241.1 (K), D251.1 (K), D261.1 (K), D271.1 (K), D281.1 (K), D291.1 (K), U_LH_0.2 (RX1/PD2), U_RH_1.2 (RX1/PD2)
Row2: D302.1 (K), D312.1 (K), D322.1 (K), D332.1 (K), D342.1 (K), D352.1 (K), D362.1 (K), D372.1 (K), D382.1 (K), D392.1 (K), U_LH_0.7 (4/PD4), U_RH_1.7 (4/PD4)
Row3: D403.1 (K), D413.1 (K), D423.1 (K), D433.1 (K), D443.1 (K), D453.1 (K), D463.1 (K), D473.1 (K), D483.1 (K), D493.1 (K), U_LH_0.8 (5/PC6), U_RH_1.8 (5/PC6)
Row4: D504.1 (K), D514.1 (K), D524.1 (K), D544.1 (K), D554.1 (K), D564.1 (K), D574.1 (K), D584.1 (K), D594.1 (K), U_LH_0.9 (6/PD7), U_RH_1.9 (6/PD7)
TRRS_D0: R1.2, U1.4 (RING2), U_LH_0.6 (3/PD0), U_RH_1.6 (3/PD0)
TRRS_D1: R2.2, U1.3 (RING1), U_LH_0.5 (2/PD1), U_RH_1.5 (2/PD1)
VCC: R1.1, R2.1, U1.1 (SLEEVE), U_LH_0.21 (VCC), U_RH_1.21 (VCC)

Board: 2 copper layers, 126 parts (0 on the bottom side), 68 nets, no tracks yet.

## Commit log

2020-06-17 Initial project file creation
2020-06-17 Add external libraries to project
2020-06-17 Major components and first rows
2020-06-17 First full schematic draft
2020-06-17 Label D and MX in schematic
2020-06-19 Divide into TKL and fullsize, annotate
2020-06-20 Initial PCB org. WIP
2020-06-20 Further PCB WIP
2020-06-20 Diodes placed
2020-06-23 Completion of first draft
2020-06-23 Update LICENSE to use markdown language
2020-06-23 Small text update
2020-06-24 File Cleanup
2020-06-24 Major revisions to schema
2020-06-24 Further major revisions
2020-06-24 Second tracing draft
2020-06-24 Adjustments to crystal placement
2020-07-01 Update fp-info-cache
2020-07-06 Adjusting gitignore
2020-07-06 Add ground fill
2020-07-06 Start reworking routing again
2020-07-06 Start adding plate
2020-07-07 Further progress
2020-07-08 Backup prior to adding silkscreen
2020-07-09 Just about ready to send to JLCPCB
2020-07-09 Needed some changes
2020-07-13 Sketch up split railroad
2020-07-13 Footprints and switch layout
2020-07-13 Update to the symmetric switch libraries
2020-07-14 Update Reset Switch and routing
2020-07-14 Submitted to JLCPCB
2020-08-27 Fix missing slot in switchplate
2020-09-01 Update Gerbers
2020-09-21 Multiple changes for better keycap compatibility
2020-09-21 Further adjustments
2020-09-24 Further alternate layouts WIP
2020-09-25 Further PCB improvements
2021-01-14 Update for new machine
2021-10-26 Clean up old files, update license
2022-07-14 miscellany

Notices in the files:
README.md:
CC BY-SA 4.0
